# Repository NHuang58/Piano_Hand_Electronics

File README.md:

# Piano-Hand-API
API using Music 21 and MIDI to convert midi files and piano notes to coordinates for a piano hand.

The KiCAD files have a full PCB design for the barrel jack, LM2896, motor servers, stepper motor driver, and microphone. This includes the Gerber files, drill files, and bill of materials. It also includes the libraries for the symbols and footprints used in this project.

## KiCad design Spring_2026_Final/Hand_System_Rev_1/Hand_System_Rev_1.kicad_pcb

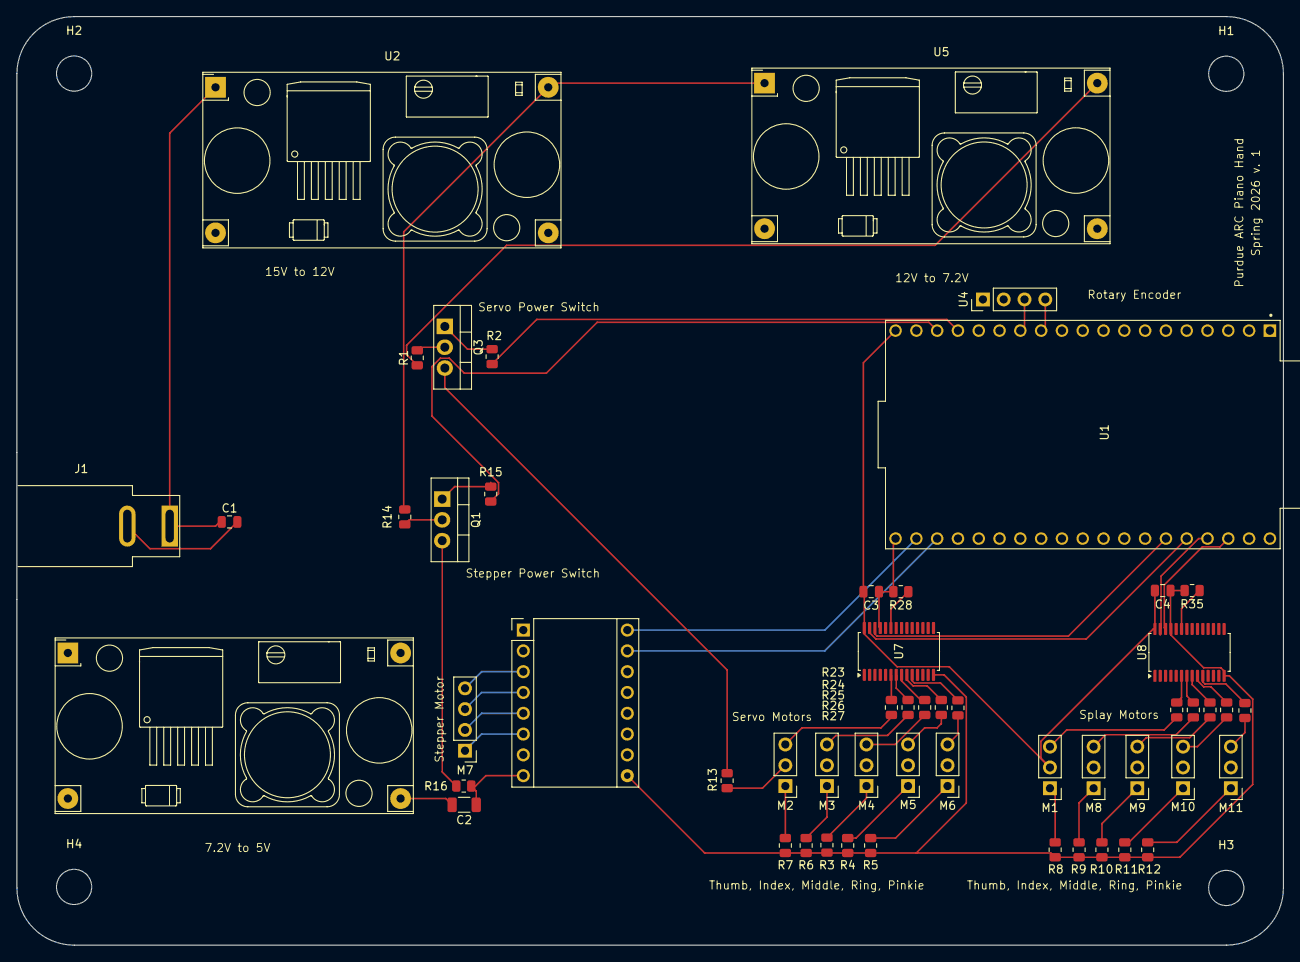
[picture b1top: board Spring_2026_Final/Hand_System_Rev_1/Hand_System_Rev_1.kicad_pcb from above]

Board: 4 copper layers, 154.7 x 113.3 mm, 58 parts (0 on the bottom side), 59 nets.

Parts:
C1: 22u; C_0805_2012Metric
C2: 100 μF; C_1206_3216Metric
C3, C4: 10uF; C_0805_2012Metric
H1, H2, H3, H4: MountingHole; MountingHole_4.3mm_M4
J1: Barrel_Jack; BarrelJack_SwitchcraftConxall_RAPC10U_Horizontal
M1, M2, M3, M4, M5, M6, M8, M9, M10, M11: Motor_Servo; PinHeader_1x03_P2.54mm_Vertical
M7: Stepper_Motor; PinHeader_1x04_P2.54mm_Vertical
Q1, Q3: IRLZ44N; TO-220-3_Vertical
R1, R14, R28, R35: 10k; R_0805_2012Metric
R2, R15: 100; R_0805_2012Metric
R3, R4, R5, R6, R7, R8, R9, R10, R11, R12: 1K; R_0805_2012Metric
R13, R16: 1k; R_0805_2012Metric
R23, R24, R25, R26, R27, R36, R37, R38, R39, R40: 220; R_0805_2012Metric
U1: ESP32-DEVKITC-32UE; MODULE_DEVKIT_V1_ESP32-WROOM-32
U2, U5, U6: LM2596
U3: A4988_Stepper_Motor_Driver; Pololu_Breakout-16_15.2x20.3mm
U4: PinHeader_1x04_P2.54mm_Vertical
U7, U8: PCA9685PW; TSSOP-28_4.4x9.7mm_P0.65mm

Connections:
5V: C3.2, C4.2, M1.2 (+), M8.2 (+), M9.2 (+), M10.2 (+), M11.2 (+), U1.19 (5V), U3.2 (VDD), U4.1 (VCC), U6.4 (Vout), U7.28 (VDD), U8.28 (VDD)
7.2V: R1.1, U5.4 (Vout), U6.1 (Vin)
12V: R14.2, U2.4 (Vout), U5.1 (Vin)
15V: C1.1, J1.1, U2.1 (Vin)
/CW: U1.13 (12), U4.3 (CW)
/DIR_PIN: U1.21 (23), U3.16 (DIR)
/DT: U1.12 (14), U4.4 (DT)
/INDEX_1: M8.3 (-), R37.1
/INDEX_2: M3.3 (PWM), R24.1
/MIDDLE_1: M9.3 (-), R38.1
/MIDDLE_2: M4.3 (PWM), R25.1
/PINKIE_1: M11.3 (-), R40.1
/PINKIE_2: M6.3 (PWM), R27.1
/RING_1: M10.3 (-), R39.1
/RING_2: M5.3 (PWM), R26.1
/SCL_SERV: U1.33 (0), U7.26 (SCL)
/SCL_SPL: U1.36 (D1), U8.26 (SCL)
/SDA_SERV: U1.34 (2), U7.27 (SDA)
/SDA_SPL: U1.35 (15), U8.27 (SDA)
/SERVO_VG: R2.1, U1.16 (D2)
/STEP_PIN: U1.22, U3.15 (STEP)
/STP_VG: R15.1, U1.17 (D3)
/THUMB_1: M1.3 (PWM), R36.1
/THUMB_2: M2.3 (PWM), R23.1
GND: C1.2, C2.2, C3.1, C4.1, J1.2, R3.1, R4.1, R5.1, R6.1, R7.1, R8.1, R9.1, R10.1, R11.1, R12.1, R28.2, R35.2, U1.14 (GND), U1.20 (GND__1), U1.26 (GND__2), U2.2 (GND), U2.3 (GND), U3.1 (GND), U3.7 (GND), U3.9 (~ENABLE), U4.2 (GND), U5.2 (GND), U5.3 (GND), U6.2 (GND), U6.3 (GND), U7.14 (VSS), U7.25 (EXTCLK), U8.14 (VSS), U8.25 (EXTCLK)
MOTOR_P: M2.2 (+), M3.2 (+), M4.2 (+), M5.2 (+), M6.2 (+), R13.2
unnamed: M1.1 (-), R8.2
unnamed: M2.1 (-), R7.2
unnamed: M3.1 (-), R6.2
unnamed: M4.1 (-), R3.2
unnamed: M5.1 (-), R4.2
unnamed: M6.1 (-), R5.2
unnamed: M7.2 (-), U3.5 (2A)
unnamed: M8.1 (PWM), R9.2
unnamed: M9.1 (PWM), R10.2
unnamed: M10.1 (PWM), R11.2
unnamed: M11.1 (PWM), R12.2
unnamed: Q1.2 (D), R14.1
unnamed: Q1.1 (G), R15.2
unnamed: Q1.3 (S), R16.1
unnamed: Q3.2 (D), R1.2
unnamed: Q3.1 (G), R2.2
unnamed: Q3.3 (S), R13.1
unnamed: M7.3, U3.4 (1A)
unnamed: M7.4, U3.3 (1B)
unnamed: M7.1, U3.6 (2B)
unnamed: R23.2, U7.6 (LED0)
unnamed: R24.2, U7.7 (LED1)
unnamed: R25.2, U7.8 (LED2)
unnamed: R26.2, U7.9 (LED3)
unnamed: R27.2, U7.10 (LED4)
unnamed: R28.1, U7.23 (~OE)
unnamed: R36.2, U8.6 (LED0)
unnamed: R37.2, U8.7 (LED1)
unnamed: R38.2, U8.8 (LED2)
unnamed: R39.2, U8.9 (LED3)
unnamed: R40.2, U8.10 (LED4)
unnamed: R35.1, U8.23 (~OE)
STP_P: C2.1, R16.2, U3.8 (VMOT)

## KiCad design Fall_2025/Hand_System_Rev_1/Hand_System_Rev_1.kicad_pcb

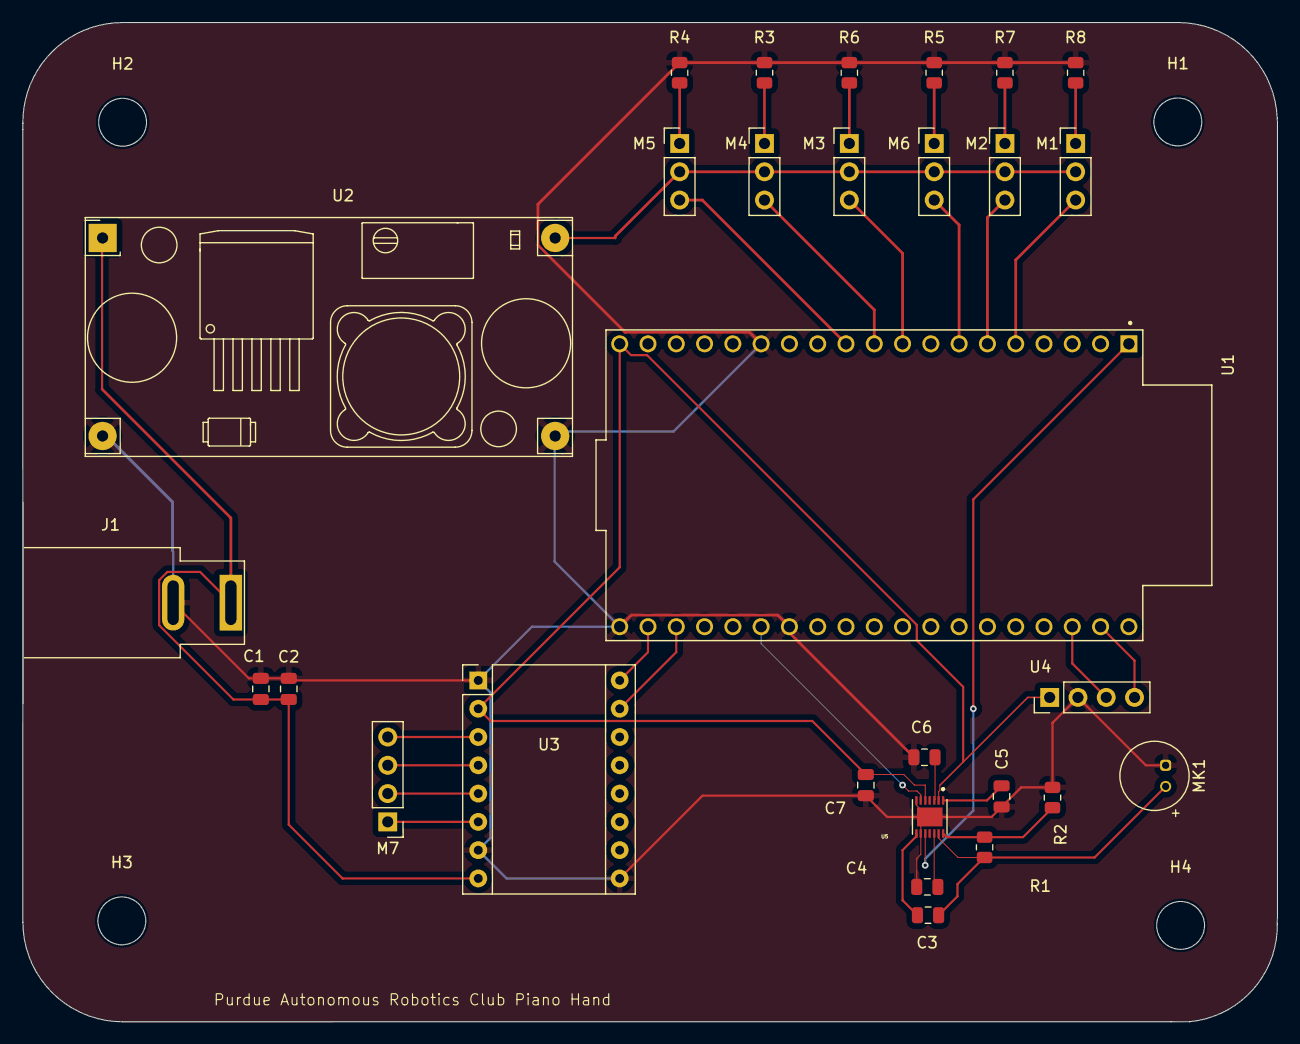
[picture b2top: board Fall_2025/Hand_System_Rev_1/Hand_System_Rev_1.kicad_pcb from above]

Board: 2 copper layers, 112.6 x 89.7 mm, 33 parts (0 on the bottom side), 32 nets.

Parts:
C1: 22u; C_0805_2012Metric
C2: 100 μF; C_0805_2012Metric
C3: 0.1uF; C_0805_2012Metric
C4: 0.47uF; C_0805_2012Metric
C5: 470nF; C_0805_2012Metric
C6: 2.2uF; C_0805_2012Metric
C7: 1uF; C_0805_2012Metric
H1, H2, H3, H4: MountingHole; MountingHole_4.3mm_M4
J1: Barrel_Jack; BarrelJack_SwitchcraftConxall_RAPC10U_Horizontal
M1, M2, M3, M4, M5, M6: Motor_Servo; PinHeader_1x03_P2.54mm_Vertical
M7: Stepper_Motor; PinHeader_1x04_P2.54mm_Vertical
MK1: Microphone; POM-2244P-C3310-2-R
R1: 150k; R_0805_2012Metric
R2: 100k; R_0805_2012Metric
R3, R4, R5, R6, R7, R8: 1K; R_0805_2012Metric
U1: ESP32-DEVKITC-32UE; MODULE_DEVKIT_V1_ESP32-WROOM-32
U2: LM2596
U3: A4988_Stepper_Motor_Driver; Pololu_Breakout-16_15.2x20.3mm
U4: PinHeader_1x04_P2.54mm_Vertical
U5: MAX9814ETD_T; SON40P300X300X80-15N

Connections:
3.3V: U1.1 (3V3), U5.10 (GAIN)
5V: C7.1, U1.19 (5V), U3.2 (VDD), U4.1 (VCC), U5.2 (~SHDN), U5.5 (VDD)
7.2V: M1.2 (+), M2.2 (+), M3.2 (+), M4.2 (+), M5.2 (+), M6.2 (+), U2.4 (Vout)
12V: C1.1, C2.1, J1.1, U2.1 (Vin), U3.8 (VMOT)
/CW: U1.36 (D1), U4.3 (CW)
/DIR_PIN: U1.21 (23), U3.16 (DIR)
/DT: U1.37 (D0), U4.4 (DT)
/INDEX: M3.3 (PWM), U1.9 (25)
/MIDDLE: M4.3 (PWM), U1.10 (26)
/MP_OUT: U1.25 (21), U5.6 (MICOUT)
/PINKIE: M6.3 (PWM), U1.7 (32)
/RING: M5.3 (PWM), U1.11 (27)
/STEP_PIN: U1.22, U3.15 (STEP)
/THUMB_1: M1.3 (PWM), U1.5 (34)
/THUMB_2: M2.3 (PWM), U1.6 (35)
GND: C1.2, C2.2, C4.1, C5.1, C6.1, C7.2, J1.2, MK1.1 (-), R2.2, R3.1, R4.1, R5.1, R6.1, R7.1, R8.1, U1.14 (GND), U1.20 (GND__1), U1.26 (GND__2), U2.2 (GND), U2.3 (GND), U3.1 (GND), U3.7 (GND), U3.9 (~ENABLE), U4.2 (GND), U5.7 (GND), U5.9 (A/R), U5.15 (EP)
unnamed: M1.1 (-), R8.2
unnamed: M2.1 (-), R7.2
unnamed: M3.1 (-), R6.2
unnamed: M4.1 (-), R3.2
unnamed: M5.1 (-), R4.2
unnamed: M6.1 (-), R5.2
unnamed: M7.2 (-), U3.5 (2A)
unnamed: C3.1, MK1.2 (+), R1.1, U5.13 (MICBIAS)
unnamed: M7.3, U3.4 (1A)
unnamed: M7.4, U3.3 (1B)
unnamed: M7.1, U3.6 (2B)
unnamed: C4.2, U5.12 (BIAS)
unnamed: C6.2, U5.3 (CG)
unnamed: C5.2, U5.1 (CT)
unnamed: C3.2, U5.8 (MICIN)
unnamed: R1.2, R2.1, U5.14 (TH)

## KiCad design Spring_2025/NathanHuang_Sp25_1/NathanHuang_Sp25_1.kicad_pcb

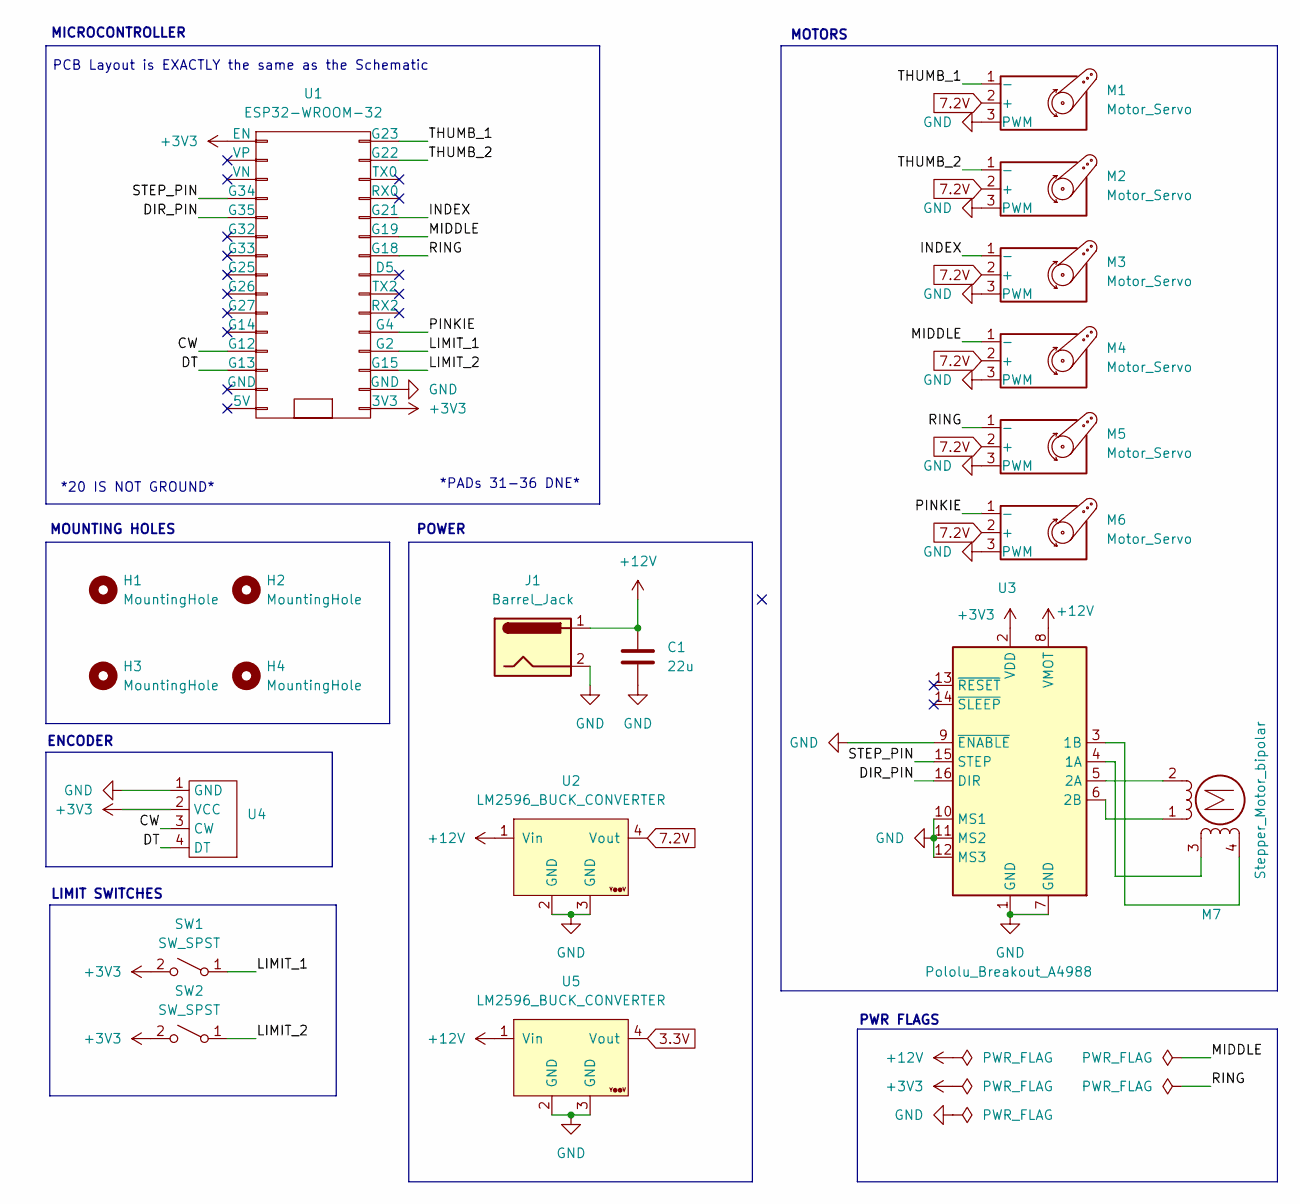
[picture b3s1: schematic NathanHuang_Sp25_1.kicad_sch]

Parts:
C1: 22u; CP_Radial_D4.0mm_P1.50mm
H1, H2, H3, H4: MountingHole; MountingHole_5.3mm_M5
J1: Barrel_Jack; BarrelJack_SwitchcraftConxall_RAPC10U_Horizontal
M1, M2, M3, M4, M5, M6: Motor_Servo; PinHeader_1x03_P2.54mm_Vertical
M7: Stepper_Motor_bipolar; PinHeader_1x04_P2.54mm_Vertical
SW1, SW2: SW_SPST; PinHeader_1x02_P2.54mm_Vertical
U1: ESP32-WROOM-32
U2, U5: LM2596_BUCK_CONVERTER
U3: Pololu_Breakout_A4988; Pololu_Breakout-16_15.2x20.3mm
U4: PinHeader_1x04_P2.54mm_Vertical

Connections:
7.2V: M1.2 (+), M2.2 (+), M3.2 (+), M4.2 (+), M5.2 (+), M6.2 (+), U2.4 (Vout)
+3V3: SW1.2 (B), SW2.2 (B), U1.1 (EN), U1.30 (3V3), U3.2 (VDD), U4.2 (VCC)
+12V: C1.1, J1.1, U2.1 (Vin), U3.8 (VMOT), U5.1 (Vin)
/CW: U1.12 (G12), U4.3 (CW)
/DIR_PIN: U1.5 (G35), U3.16 (DIR)
/DT: U1.13 (G13), U4.4 (DT)
/INDEX: M3.1 (-), U1.20 (G21)
/LIMIT_1: SW1.1 (A), U1.27 (G2)
/LIMIT_2: SW2.1 (A), U1.28 (G15)
/MIDDLE: M4.1 (-), U1.21 (G19)
/PINKIE: M6.1 (-), U1.26 (G4)
/RING: M5.1 (-), U1.22 (G18)
/STEP_PIN: U1.4 (G34), U3.15 (STEP)
/THUMB_1: M1.1 (-), U1.16 (G23)
/THUMB_2: M2.1 (-), U1.17 (G22)
GND: C1.2, J1.2, M1.3 (PWM), M2.3 (PWM), M3.3 (PWM), M4.3 (PWM), M5.3 (PWM), M6.3 (PWM), U1.29 (GND), U2.2 (GND), U2.3 (GND), U3.1 (GND), U3.7 (GND), U3.9 (~ENABLE), U3.10 (MS1), U3.11 (MS2), U3.12 (MS3), U4.1 (GND), U5.2 (GND), U5.3 (GND)
unnamed: M7.2 (-), U3.5 (2A)
unnamed: M7.3, U3.4 (1A)
unnamed: M7.4, U3.3 (1B)
unnamed: M7.1, U3.6 (2B)

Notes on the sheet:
MOTORS
MICROCONTROLLER
ENCODER
PWR FLAGS
POWER
LIMIT SWITCHES
PCB Layout is EXACTLY the same as the Schematic
*20 IS NOT GROUND*
MOUNTING HOLES
*PADs 31-36 DNE*

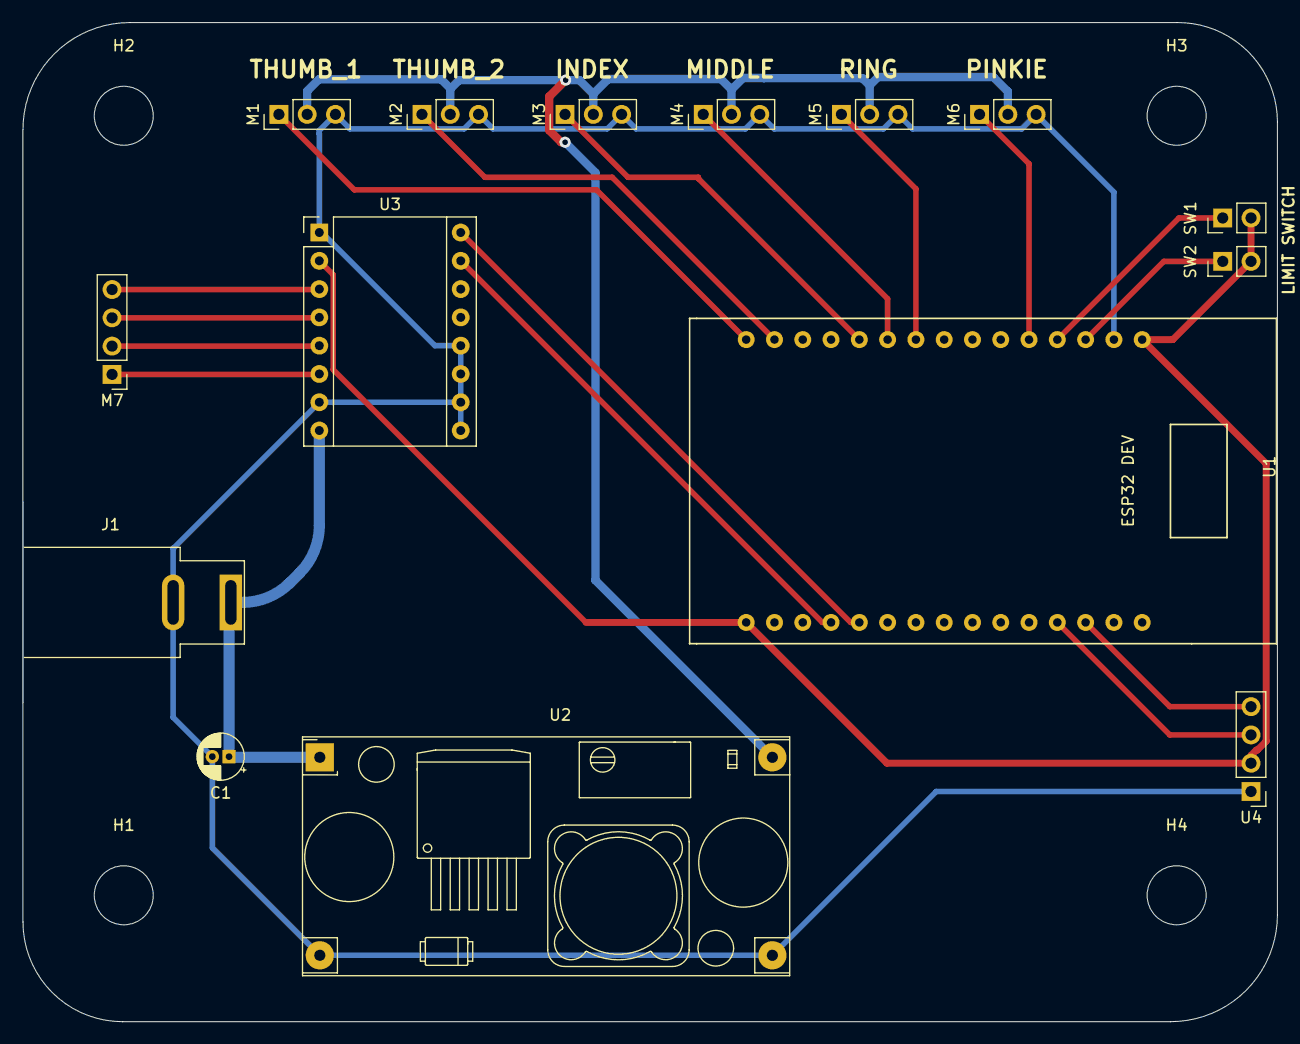
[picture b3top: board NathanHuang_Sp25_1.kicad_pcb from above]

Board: 2 copper layers, 112.6 x 89.7 mm, 19 parts (0 on the bottom side), 20 nets.

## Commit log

2025-02-01 Create encoder
2025-02-01 New Repository
2025-02-01 Rotary Encoder
2025-02-08 Added Psuedocode
2025-02-08 Change
2025-02-08 Added one line
2025-03-01 added new folder
2025-03-01 Version 3 PCB
2025-03-01 Added Footprints
2025-03-07 Schematic Changes
2025-03-08 footprint added
    for stepper motor driver
2025-03-08 Library
2025-03-08 Schematic Done
2025-03-08 Routed PCB
2025-03-08 PCB Changes
2025-03-09 Finished PCB, Ready for Print
2025-03-29 PCB Updates
2025-04-05 4/4 Changes
2025-04-05 Found Footprint
    New to find new schematic for 30 pin
2025-04-11 Overwrite Changes
2025-04-12 Don't clone
2025-04-12 Updated PCB schematic
2025-04-12 Random
2025-04-12 push
2025-04-12 pushhh
2025-04-19 Gerbers ready
2025-04-19 PCB V4 Done
2025-04-26 Gerber Files
2025-10-16 Added files for MAX 9814
2025-10-16 Found footprints
2025-10-16 Updated MAX9814
2025-10-16 File Changes
2025-10-16 Updated files for esp32 devkitc
2025-10-16 10-16-25 Changes
2025-11-02 added microphone
2025-11-03 creating kicad pcb schematic
2025-12-11 Finalized the pcb design
    Included microphone and other modules.
    Successfully got gerber files, drill files, and bom
2025-12-11 Update README with KiCAD and PCB design information
    Added details about KiCAD files and PCB design.
2026-02-21 update electrical schematic to include 10 servo motors, two buck converteds, and removed microphone
2026-02-22 added more stuff for switching circuitry
2026-03-04 added more stuff
2026-03-04 new project in spring 2026
2026-03-04 more stuff for organizing into spring 2026
2026-03-05 Moved Buck converter down
2026-03-07 Finished pcb design spring 2026
2026-03-07 Added buck converter 12v to 5v.
2026-03-07 Made PCB with fixed buck coverter 12V to 5v.
2026-04-09 finish pcb design
2026-06-10 Final Changes
